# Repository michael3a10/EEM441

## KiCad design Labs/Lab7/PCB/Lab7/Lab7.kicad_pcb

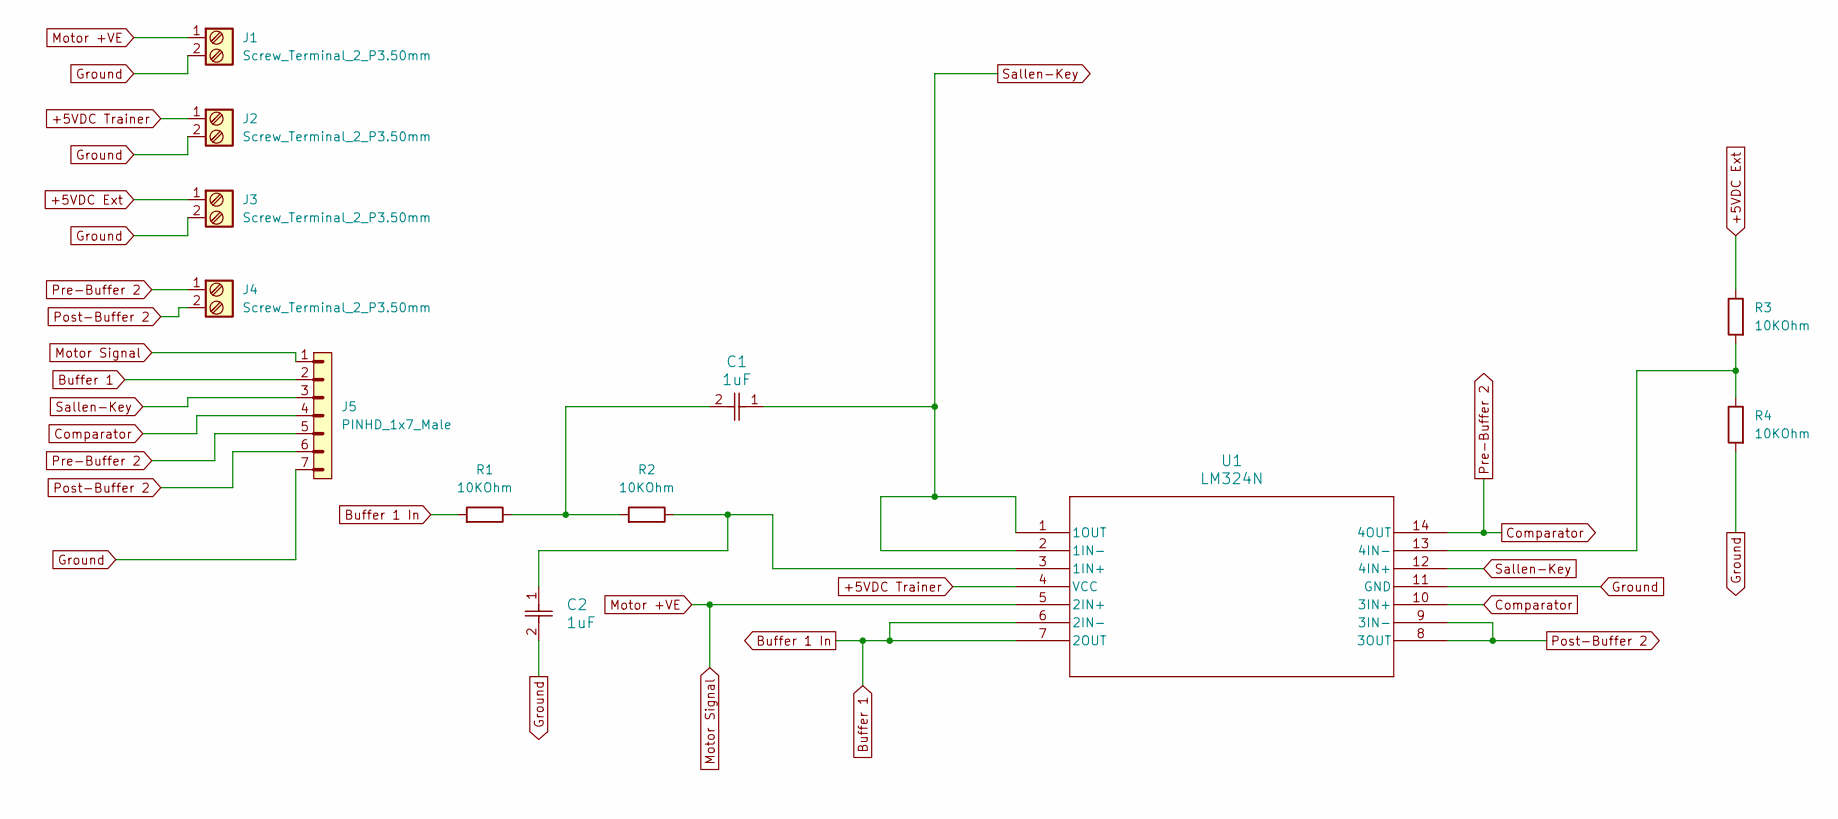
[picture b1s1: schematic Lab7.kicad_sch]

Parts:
C1, C2: 1uF; CAP_YX_5X11_RUB
J1, J2, J3, J4: Screw_Terminal_2_P3.50mm; TerminalBlock_MaiXu_MX126-5.0-02P_1x02_P5.00mm
J5: PINHD_1x7_Male; PinHeader_1x07_P2.54mm_Vertical
R1, R2, R3, R4: 10KOhm; R_Axial_DIN0204_L3.6mm_D1.6mm_P5.08mm_Horizontal
U1: LM324N

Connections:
+5VDC Ext: J3.1, R3.2
+5VDC Trainer: J2.1, U1.4 (VCC)
Buffer 1: J5.2, R1.1, U1.6 (2IN-), U1.7 (2OUT)
Comparator: J4.1, J5.4, J5.5, U1.10 (3IN+), U1.14 (4OUT)
Ground: C2.2, J1.2, J2.2, J3.2, J5.7, R4.1, U1.11 (GND)
Motor +VE: J1.1, J5.1, U1.5 (2IN+)
unnamed: C1.2, R1.2, R2.1
unnamed: C2.1, R2.2, U1.3 (1IN+)
unnamed: R3.1, R4.2, U1.13 (4IN-)
Post-Buffer 2: J4.2, J5.6, U1.8 (3OUT), U1.9 (3IN-)
Sallen-Key: C1.1, J5.3, U1.1 (1OUT), U1.2 (1IN-), U1.12 (4IN+)

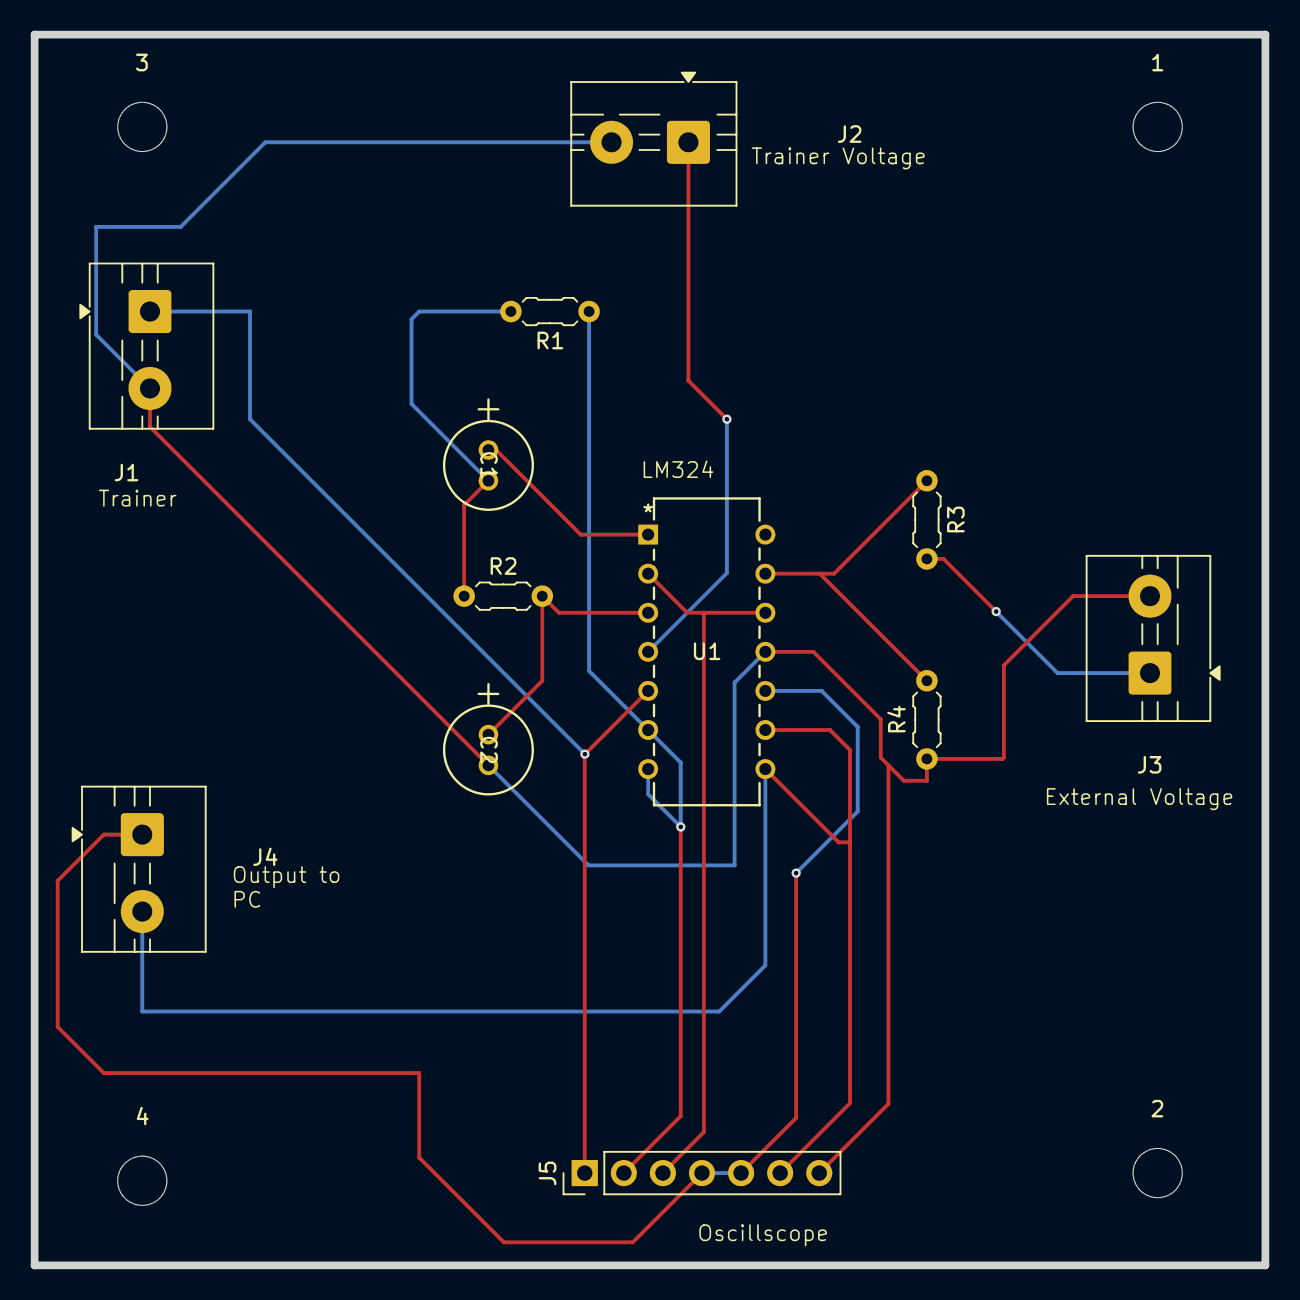
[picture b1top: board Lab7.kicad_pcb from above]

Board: 2 copper layers, 80.0 x 80.0 mm, 16 parts (0 on the bottom side), 11 nets.

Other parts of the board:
1, 2, 3, 4: MountingHole_3.2mm_M3

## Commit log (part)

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2025-09-16 Added lab manual folders
2025-09-16 updates
    created folders for each lab and versions
